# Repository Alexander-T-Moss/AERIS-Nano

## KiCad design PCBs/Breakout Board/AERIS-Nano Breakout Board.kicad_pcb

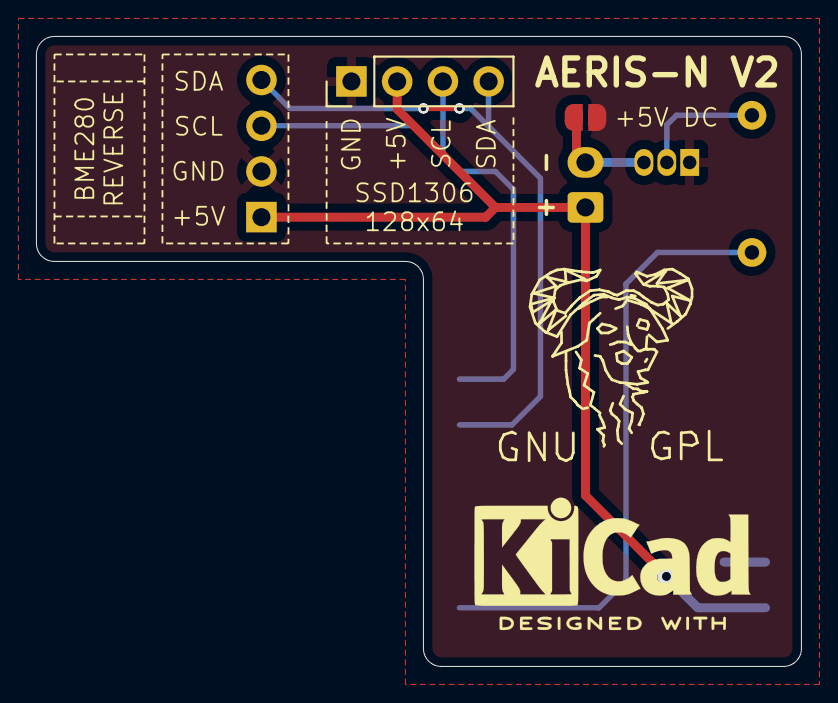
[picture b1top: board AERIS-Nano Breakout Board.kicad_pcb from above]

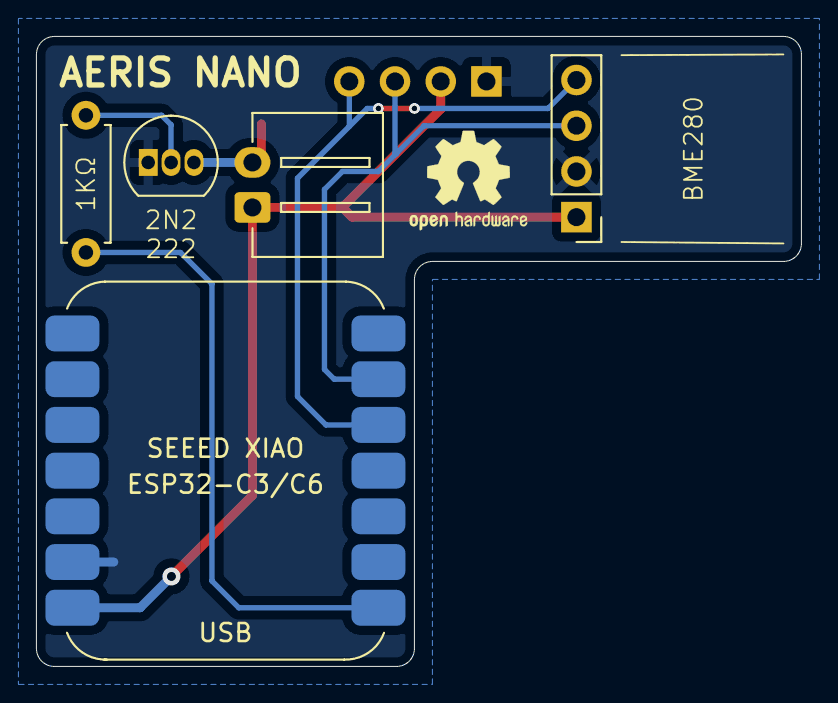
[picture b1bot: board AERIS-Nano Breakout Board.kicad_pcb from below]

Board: 2 copper layers, 42.5 x 35.0 mm, 7 parts (5 on the bottom side), 7 nets.

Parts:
DC: DC Jumper; SolderJumper-2_P1.3mm_Open_RoundedPad1.0x1.5mm
J1, J2: Conn_01x04_Pin; PinHeader_1x04_P2.54mm_Vertical
J3: Conn_01x02_Socket; JST_XH_S2B-XH-A-1_1x02_P2.50mm_Horizontal
Q1: 2N2222; TO-92_Inline
R1: 1K; R_Axial_DIN0207_L6.3mm_D2.5mm_P7.62mm_Horizontal
U1: ESP32C3; XIAO_ESP32

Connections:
+5V: J1.2, J2.1, J3.1, U1.14 (VUSB)
/PWM: R1.1, U1.1 (D0)
/SCL: J1.3, J2.3, U1.6 (D5)
/SDA: J1.4, J2.4, U1.5 (D4)
GND: DC.2 (B), J1.1, J2.2, Q1.1 (E), U1.13 (GND)
unnamed: DC.1 (A), J3.2, Q1.3 (C)
unnamed: Q1.2 (B), R1.2

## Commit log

2025-08-29 Remove duplicate
2025-08-29 Update PCB
2025-09-04 Add PCB CAD
    Also updated silkscreen
2025-09-04 Make footprints project and not global
2025-10-05 PCB V2
